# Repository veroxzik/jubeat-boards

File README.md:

# jubeat-boards
A collection of boards related to jubeat things.

## jubeat-button-pcb

This is a clone of the button PCB located in the panel (qty 8 per panel). See its readme for more information.

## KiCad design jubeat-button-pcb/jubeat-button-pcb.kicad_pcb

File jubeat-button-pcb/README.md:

# jubeat-button-pcb

There is only one component on the board:

|Mfg|Part No.|Qty|
|:---:|:---|:---:|
|JST|S9B-PH-K|1|

This item is no longer manufactured by JST, but the following connectors are drop-in replacements:

Digikey:
* https://www.digikey.com/en/products/detail/adam-tech/2SH-C-09-TR/9830823
* https://www.digikey.com/en/products/detail/te-connectivity-amp-connectors/440055-9/2077953
* https://www.digikey.com/en/products/detail/te-connectivity-amp-connectors/292253-9/1855251

LCSC:
* https://lcsc.com/product-detail/Wire-To-Board-Wire-To-Wire-Connector_BOOMELE-Boom-Precision-Elec-PH-9AWD_C82518.html
* https://lcsc.com/product-detail/Wire-To-Board-Wire-To-Wire-Connector_BOOMELE-Boom-Precision-Elec-PH-9AW_C10404.html

## How to order this board

Upload `jubeat-button-pcb_v1.0.zip` from the `gerbers` folder to your favorite PCB website. JLCPCB is a common one.

For best performance, choose ENIG for your surface finish. This will increase cost by quite a bit, but will significantly reduce the level of corrosion you can expect over the lifetime of the boards. It's up to you.

All other settings can remain the defaults. Thickness should be 1.6 mm.

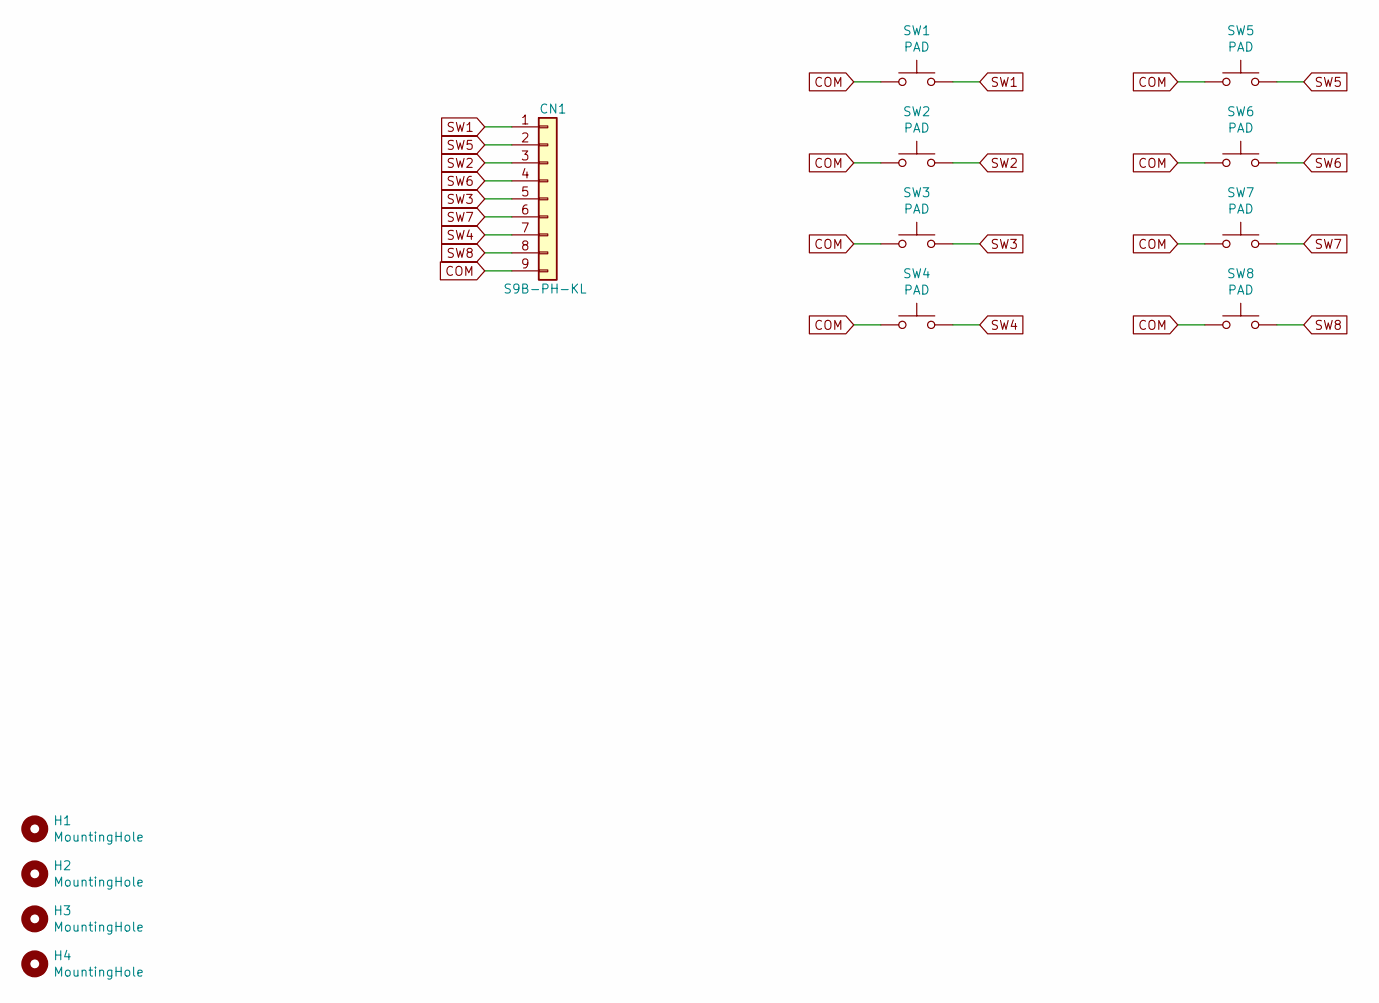
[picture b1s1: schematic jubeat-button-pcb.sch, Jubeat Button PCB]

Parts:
CN1: S9B-PH-KL; JST_PH_S9B-PH-K_1x09_P2.00mm_Horizontal
H1, H2, H3, H4: MountingHole; MountingHole_4mm
SW1, SW2, SW3, SW4, SW5, SW6, SW7, SW8: PAD; membrane-pad

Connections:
COM: CN1.9, SW1.1, SW2.1, SW3.1, SW4.1, SW5.1, SW6.1, SW7.1, SW8.1
SW1: CN1.1, SW1.2
SW2: CN1.3, SW2.2
SW3: CN1.5, SW3.2
SW4: CN1.7, SW4.2
SW5: CN1.2, SW5.2
SW6: CN1.4, SW6.2
SW7: CN1.6, SW7.2
SW8: CN1.8, SW8.2

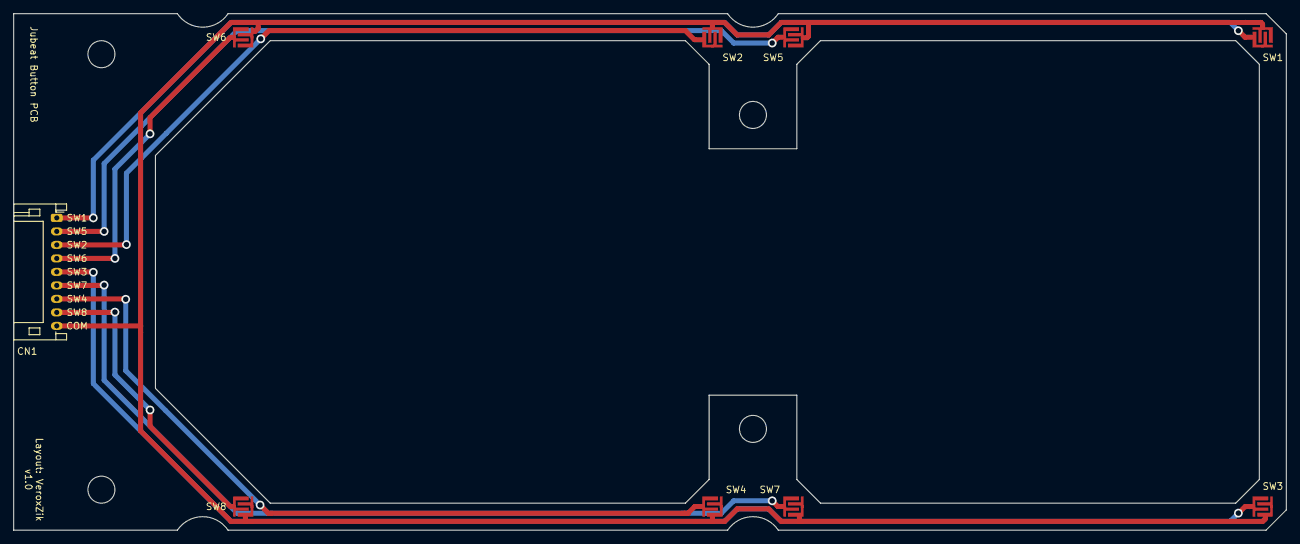
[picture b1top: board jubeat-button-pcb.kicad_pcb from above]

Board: 2 copper layers, 188.5 x 76.5 mm, 13 parts (0 on the bottom side), 9 nets.

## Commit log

2021-02-13 jubeat-button-board v1.0
    Includes kicad project and gerbers.
2021-02-14 Remove F.Paste from membrade pad footprint
2021-02-14 Add button PCB render to README.md
2022-06-03 Remove JST links since connector is EOL.
